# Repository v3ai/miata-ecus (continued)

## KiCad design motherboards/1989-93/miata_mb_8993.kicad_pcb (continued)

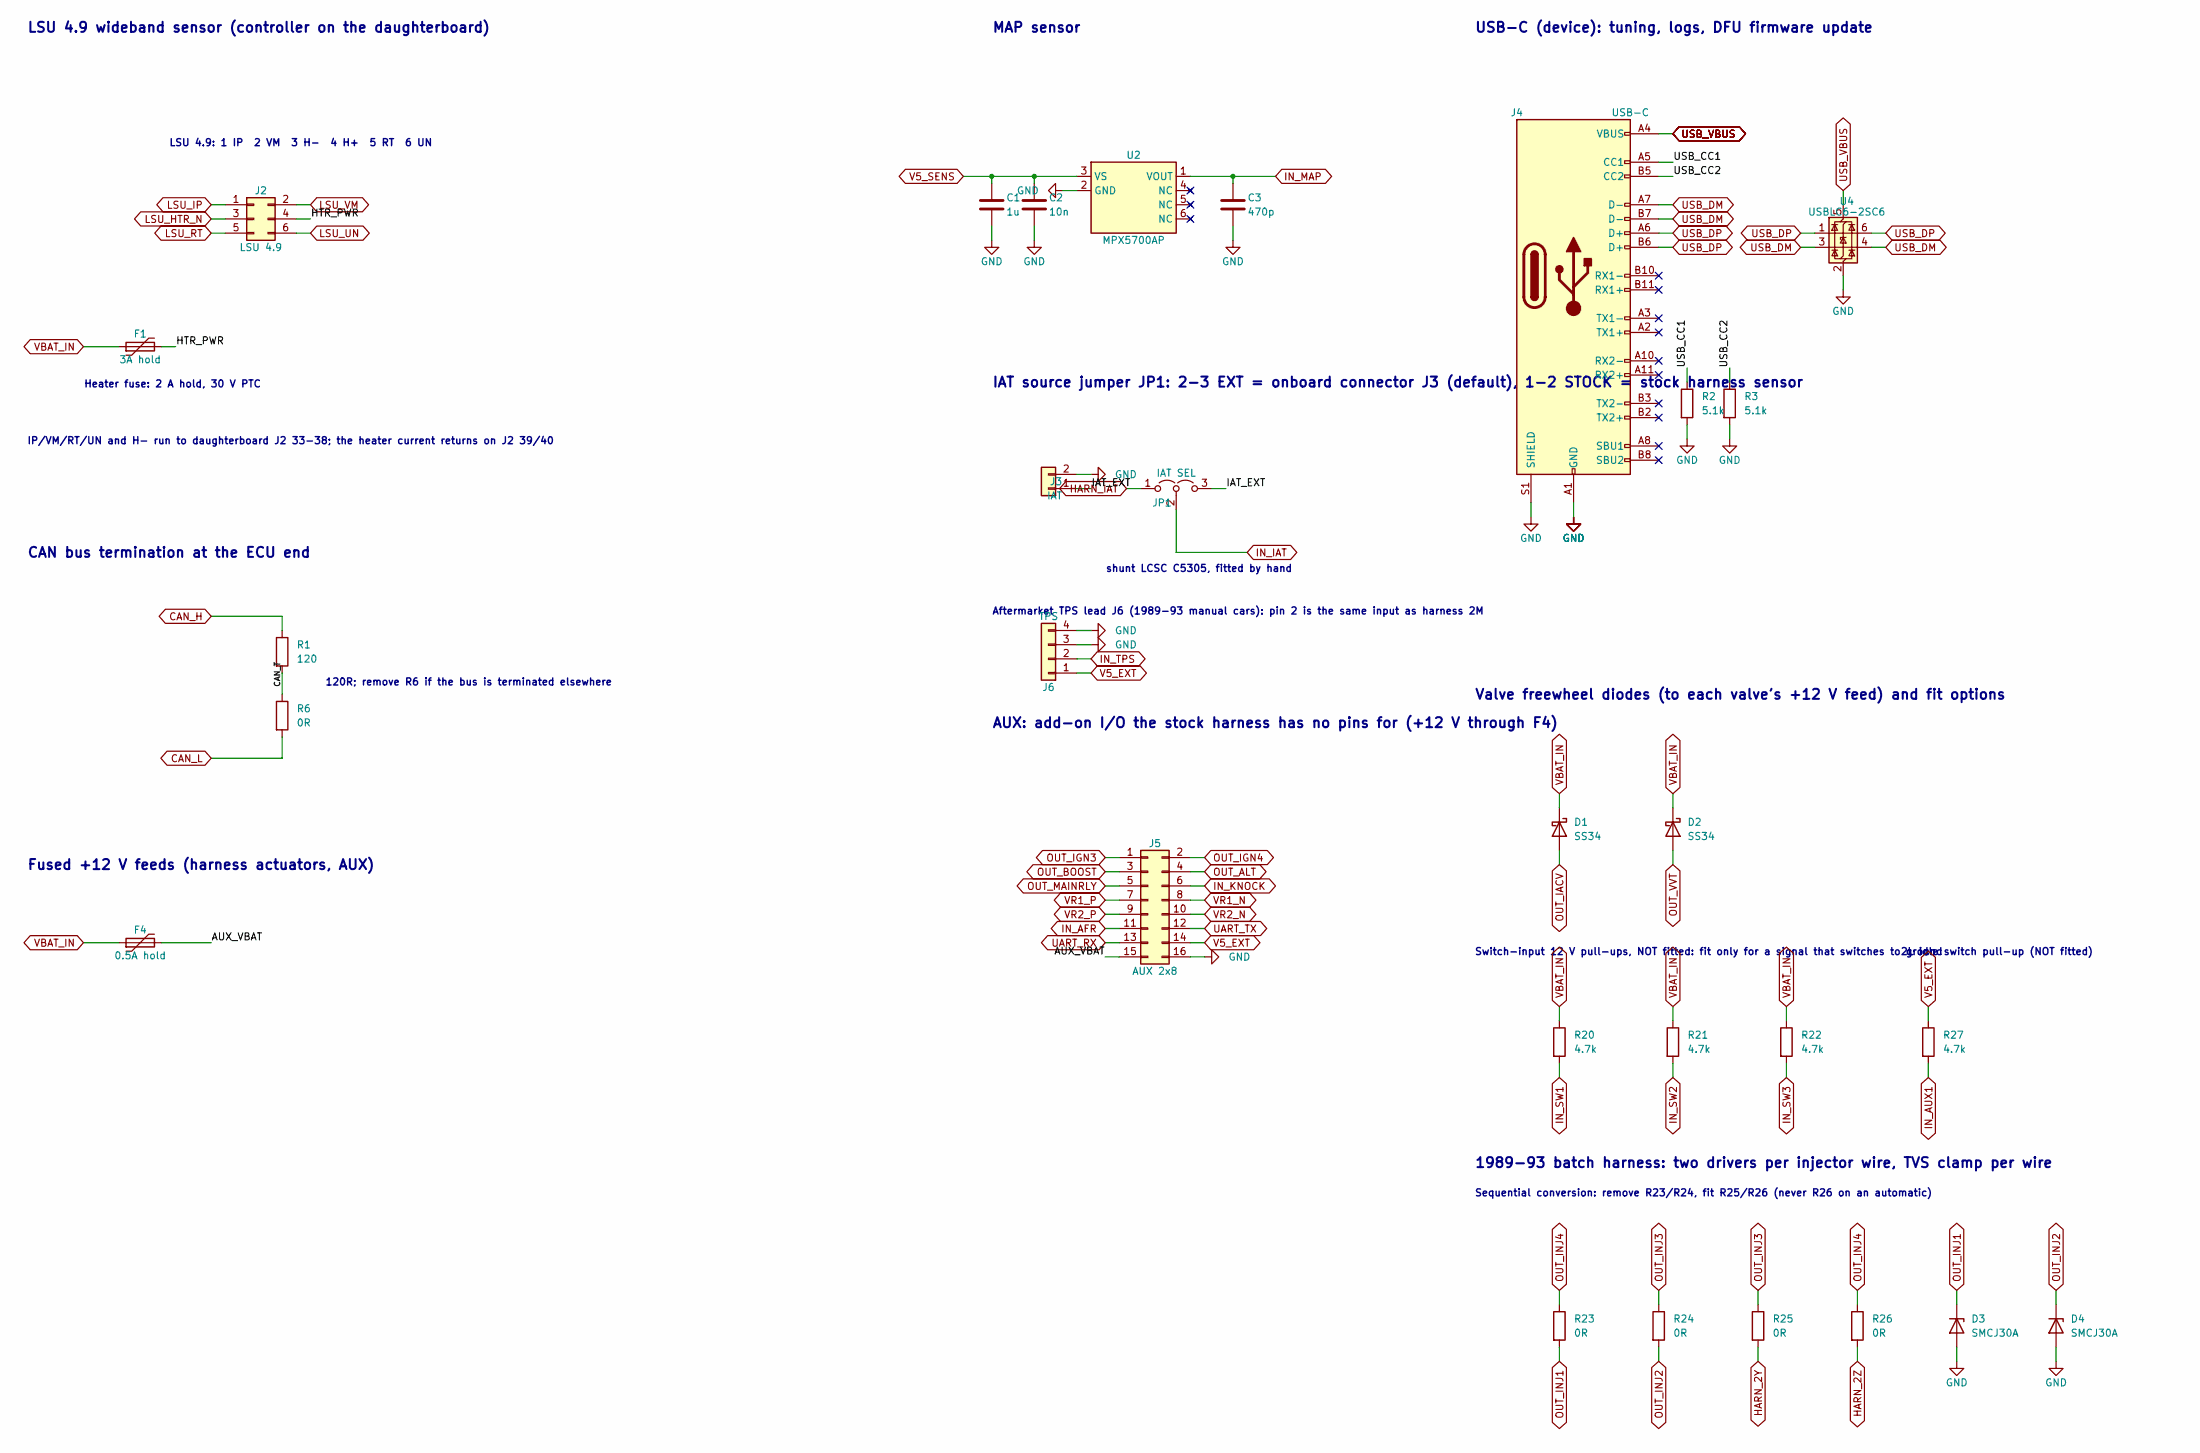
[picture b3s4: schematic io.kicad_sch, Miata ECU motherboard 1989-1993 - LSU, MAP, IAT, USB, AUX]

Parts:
C1: 1u; C_0603_1608Metric; LCSC C15849
C2: 10n; C_0603_1608Metric; LCSC C57112
C3: 470p; C_0603_1608Metric; LCSC C1620
D1, D2: SS34; D_SMA; LCSC C8678
D3, D4: SMCJ30A; D_SMC; LCSC C224048
F1: 3A hold; Fuse_2920_7451Metric; LCSC C22446884
F4: 0.5A hold; Fuse_1206_3216Metric; LCSC C70077
J2: LSU 4.9; Molex_Micro-Fit_3.0_43045-0600_2x03_P3.00mm_Horizontal; LCSC C127367
J3: IAT; Molex_Micro-Fit_3.0_43650-0200_1x02_P3.00mm_Horizontal; LCSC C587650
J4: USB-C; USB_C_GCT_USB4105_16P; LCSC C3020560
J5: AUX 2x8; IDC-Header_2x08_P2.54mm_Vertical; LCSC C3406
J6: TPS; Molex_Micro-Fit_3.0_43650-0400_1x04_P3.00mm_Horizontal; LCSC C277684
JP1: IAT SEL; PinHeader_1x03_P2.54mm_Vertical; LCSC C49257
R1: 120; R_0603_1608Metric; LCSC C22787
R2, R3: 5.1k; R_0603_1608Metric; LCSC C23186
R6: 0R; R_0603_1608Metric; LCSC C21189
R20, R21, R22, R27: 4.7k; R_0603_1608Metric
R23, R24: 0R; R_0805_2012Metric; LCSC C17477
R25, R26: 0R; R_0805_2012Metric
U2: MPX5700AP; MPX5700AP_867B_Flat; LCSC C90152
U4: USBLC6-2SC6; SOT-23-6; LCSC C7519

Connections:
/LSU, MAP, IAT, USB, AUX/AUX_VBAT: F4.2, J5.15
/LSU, MAP, IAT, USB, AUX/CAN_T: R1.2, R6.1
/LSU, MAP, IAT, USB, AUX/HTR_PWR: F1.2, J2.4
/LSU, MAP, IAT, USB, AUX/IAT_EXT: J3.1, JP1.3 (B)
/LSU, MAP, IAT, USB, AUX/USB_CC1: J4.A5 (CC1), R2.1
/LSU, MAP, IAT, USB, AUX/USB_CC2: J4.B5 (CC2), R3.1
CAN_H: R1.1; also elsewhere on the board
CAN_L: R6.2; also elsewhere on the board
GND: C1.2, C2.2, C3.2, D3.2 (A), D4.2 (A), J3.2, J4.A1 (GND), J4.A12 (GND), J4.B1 (GND), J4.B12 (GND), J4.S1 (SHIELD), J5.16, J6.3, J6.4, R2.2, R3.2, U2.2 (GND), U4.2 (GND); also elsewhere on the board
HARN_2Y: R25.2; also elsewhere on the board
HARN_2Z: R26.2; also elsewhere on the board
HARN_IAT: JP1.1 (A); also elsewhere on the board
IN_AFR: J5.11; also elsewhere on the board
IN_AUX1: R27.2; also elsewhere on the board
IN_IAT: JP1.2 (C); also elsewhere on the board
IN_KNOCK: J5.6; also elsewhere on the board
IN_MAP: C3.1, U2.1 (VOUT); also elsewhere on the board
IN_SW1: R20.2; also elsewhere on the board
IN_SW2: R21.2; also elsewhere on the board
IN_SW3: R22.2; also elsewhere on the board
IN_TPS: J6.2; also elsewhere on the board
LSU_HTR_N: J2.3; also elsewhere on the board
LSU_IP: J2.1; also elsewhere on the board
LSU_RT: J2.5; also elsewhere on the board
LSU_UN: J2.6; also elsewhere on the board
LSU_VM: J2.2; also elsewhere on the board
OUT_ALT: J5.4; also elsewhere on the board
OUT_BOOST: J5.3; also elsewhere on the board
OUT_IACV: D1.2 (A); also elsewhere on the board
OUT_IGN3: J5.1; also elsewhere on the board
OUT_IGN4: J5.2; also elsewhere on the board
OUT_INJ1: D3.1 (K), R23.2; also elsewhere on the board
OUT_INJ2: D4.1 (K), R24.2; also elsewhere on the board
OUT_INJ3: R24.1, R25.1; also elsewhere on the board
OUT_INJ4: R23.1, R26.1; also elsewhere on the board
OUT_MAINRLY: J5.5; also elsewhere on the board
OUT_VVT: D2.2 (A); also elsewhere on the board
UART_RX: J5.13; also elsewhere on the board
UART_TX: J5.12; also elsewhere on the board
USB_DM: J4.A7 (D-), J4.B7 (D-), U4.3 (I/O2), U4.4 (I/O2); also elsewhere on the board
USB_DP: J4.A6 (D+), J4.B6 (D+), U4.1 (I/O1), U4.6 (I/O1); also elsewhere on the board
USB_VBUS: J4.A4 (VBUS), J4.A9 (VBUS), J4.B4 (VBUS), J4.B9 (VBUS), U4.5 (VBUS); also elsewhere on the board
V5_EXT: J5.14, J6.1, R27.1; also elsewhere on the board
V5_SENS: C1.1, C2.1, U2.3 (VS); also elsewhere on the board
VBAT_IN: D1.1 (K), D2.1 (K), F1.1, F4.1, R20.1, R21.1, R22.1; also elsewhere on the board
VR1_N: J5.8; also elsewhere on the board
VR1_P: J5.7; also elsewhere on the board
VR2_N: J5.10; also elsewhere on the board
VR2_P: J5.9; also elsewhere on the board

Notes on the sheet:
LSU 4.9 wideband sensor (controller on the daughterboard)
LSU 4.9: 1 IP 2 VM 3 H- 4 H+ 5 RT 6 UN
IP/VM/RT/UN and H- run to daughterboard J2 33-38; the heater current returns on J2 39/40
Heater fuse: 2 A hold, 30 V PTC
CAN bus termination at the ECU end
120R; remove R6 if the bus is terminated elsewhere
MAP sensor
IAT source jumper JP1: 2-3 EXT = onboard connector J3 (default), 1-2 STOCK = stock harness sensor
shunt LCSC C5305, fitted by hand
Aftermarket TPS lead J6 (1989-93 manual cars): pin 2 is the same input as harness 2M
USB-C (device): tuning, logs, DFU firmware update
Fused +12 V feeds (harness actuators, AUX)
AUX: add-on I/O the stock harness has no pins for (+12 V through F4)
Valve freewheel diodes (to each valve's +12 V feed) and fit options
Switch-input 12 V pull-ups, NOT fitted: fit only for a signal that switches to ground
2L idle switch pull-up (NOT fitted)
1989-93 batch harness: two drivers per injector wire, TVS clamp per wire
Sequential conversion: remove R23/R24, fit R25/R26 (never R26 on an automatic)

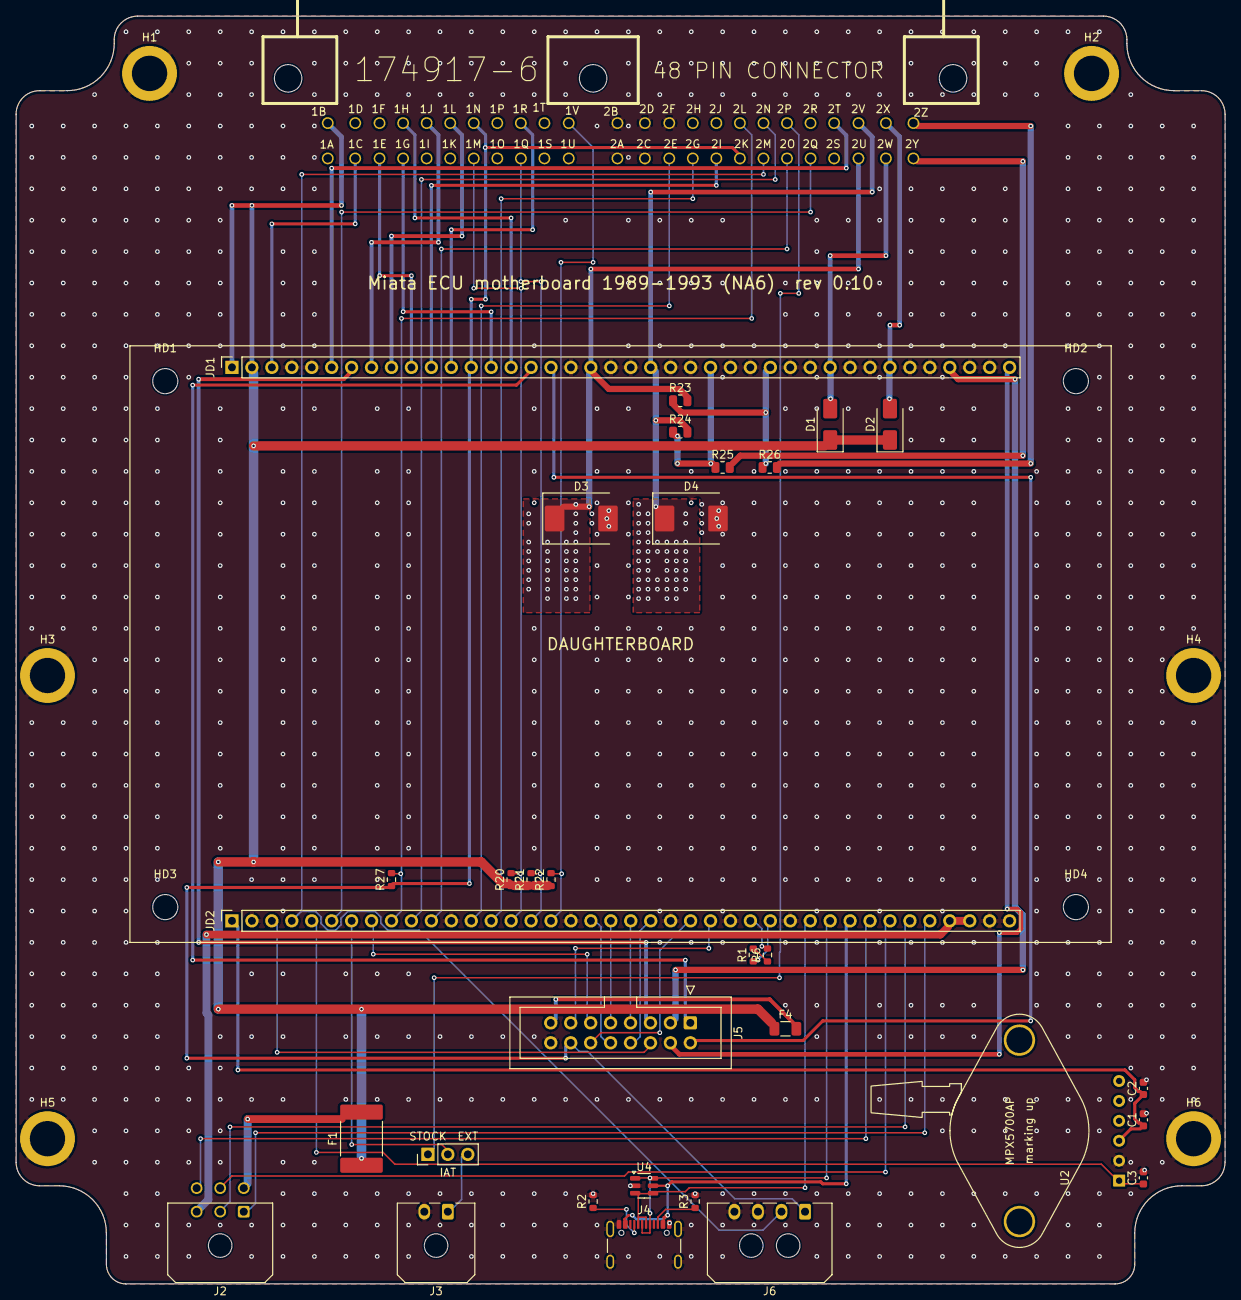
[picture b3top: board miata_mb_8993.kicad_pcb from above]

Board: 2 copper layers, 154.0 x 161.5 mm, 42 parts (0 on the bottom side), 63 nets.

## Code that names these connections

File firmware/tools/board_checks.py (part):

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Datasheet limits used (STM32F405 / F407 DS8626, STM32F103x8 DS5319; F4 family IINJ table re-confirmed in the STM32F412
datasheet, same structure):
  FT pins: VIN abs max VDD + 4.0 V; injected current -5 / +0 mA (no positive injection possible: there is no clamp
  to VDD, so the limit above VDD is the voltage, not a current). TTa (PA4/PA5) and F103 non-FT pins: VIN abs max
  4.0 V, injected current +-5 mA (diodes to VDDA / VDD). Total injected current +-25 mA. Operating range on FT pins
  -0.3..5.5 V. An FT pin used as an ADC input is treated as good to VDDA only (outside it the reading clips; tolerance
  above VDDA in analog mode is not relied on: CHECK).
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F407_NAME = {int(n): name for n, name in
             (s.split(':') for s in open(os.path.join(SCRIPTS, 'stm32f407v_lqfp100_pins.txt')).read().split())}
F407_PIN = {v: k for k, v in F407_NAME.items()}
# DS8626 pin definitions, LQFP100: every GPIO is FT except PA4/PA5 (TTa, DAC outputs); PC13-15 are FT but sit in the
# backup domain (2 MHz, 3 mA total sink/source through the power switch).
F407_TTA = {'PA4', 'PA5'}
F103_NAME = {1: 'VBAT', 2: 'PC13', 3: 'PC14', 4: 'PC15', 5: 'PD0', 6: 'PD1', 7: 'NRST', 8: 'VSSA', 9: 'VDDA',
             10: 'PA0', 11: 'PA1', 12: 'PA2', 13: 'PA3', 14: 'PA4', 15: 'PA5', 16: 'PA6', 17: 'PA7', 18: 'PB0',
             19: 'PB1', 20: 'PB2', 21: 'PB10', 22: 'PB11', 23: 'VSS', 24: 'VDD', 25: 'PB12', 26: 'PB13', 27: 'PB14',
             28: 'PB15', 29: 'PA8', 30: 'PA9', 31: 'PA10', 32: 'PA11', 33: 'PA12', 34: 'PA13', 35: 'VSS', 36: 'VDD',
             37: 'PA14', 38: 'PA15', 39: 'PB3', 40: 'PB4', 41: 'PB5', 42: 'PB6', 43: 'PB7', 44: 'BOOT0', 45: 'PB8',
             46: 'PB9', 47: 'VSS', 48: 'VDD'}
# DS5319 pin definitions: FT = PA8-PA15, PB2-PB4, PB6-PB15, PD0/PD1; not FT: PA0-PA7, PB0, PB1, PB5, PC13-PC15
F103_FT = {'PA8', 'PA9', 'PA10', 'PA11', 'PA12', 'PA13', 'PA14', 'PA15', 'PB2', 'PB3', 'PB4', 'PB6', 'PB7', 'PB8',
           'PB9', 'PB10', 'PB11', 'PB12', 'PB13', 'PB14', 'PB15', 'PD0', 'PD1'}
VDD = 3.3
LIM_FT_V = VDD + 4.0          # abs max on FT pins
LIM_NONFT_V = 4.0             # abs max on TTa / non-FT pins
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FT_OPER_MAX = 5.5
VIL, VIH = 0.3 * VDD, 0.7 * VDD   # DS8626 CMOS levels (conservative; FT inputs switch at 1.79 V by design)

ADC = {**{f'EFI_ADC_{i}': f'PA{i}' for i in range(8)}, 'EFI_ADC_8': 'PB0', 'EFI_ADC_9': 'PB1',
       **{f'EFI_ADC_{10 + i}': f'PC{i}' for i in range(6)}}

# alternate functions whose direction matters (DS8626 / DS5319 alternate-function tables)
AF_DIR = {('U1', 'PB12'): ('CAN2_RX', 'in'), ('U1', 'PB13'): ('CAN2_TX', 'out'),
          ('U1', 'PC6'): ('USART6_TX', 'out'), ('U1', 'PC7'): ('USART6_RX', 'in'),
          ('U1', 'PD8'): ('USART3_TX', 'out'), ('U1', 'PD9'): ('USART3_RX', 'in'),
          ('U102', 'PA9'): ('USART1_TX', 'out'), ('U102', 'PA10'): ('USART1_RX', 'in'),
          ('U102', 'PA11'): ('CAN_RX', 'in'), ('U102', 'PA12'): ('CAN_TX', 'out')}


def mcu_pin_info(ref, pad):
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    'vehicleSpeedSensorInputPin': 'vss', 'acSwitch': 'acSwitch', 'clutchDownPin': 'clutch',
    'tps1_1AdcChannel': 'tps', 'mafAdcChannel': 'maf', 'afr.hwChannel': 'afr', 'ignKeyAdcChannel': 'ignKey',
    'vbattAdcChannel': 'vbatt', 'clt.adcChannel': 'clt', 'iat.adcChannel': 'iat', 'map.sensor.hwChannel': 'map',
    'canTxPin': 'can2Tx', 'canRxPin': 'can2Rx',   # PB13/PB12 = CAN2 peripheral, rusEFI's first bus
}
FW_OUTPUTS = {'ign1&4', 'ign3(COP)', 'ign2&3', 'ign4(COP)', 'inj1', 'inj2', 'inj3', 'inj4', 'idle', 'fuelPump',
              'acRelay', 'fan', 'fan2', 'cel', 'tach', 'boost', 'mainRelay', 'alternator', 'vvt', 'o2heater'}
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    wb = open(os.path.join(BOARD, 'wideband_uart_flash.cpp')).read()
    for label, port in re.findall(r'efiSetPadMode\("WBO ([\w ]+)", Gpio::(\w+)', wb):
        board['wbo ' + label] = 'P' + port
    board['usbDM'], board['usbDP'], board['swdio'], board['swclk'] = 'PA11', 'PA12', 'PA13', 'PA14'
    board['uart6Tx'], board['uart6Rx'] = 'PC6', 'PC7'   # rusEFI's TS secondary / AUX UART (J5-12/13)
    return out, board, sorted(external)


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                      'o2heater', 'vvt', 'boost', 'vss', 'acSwitch', 'clutch'):
                fw[k] = kv.get(k, '-')
            fw = {k: ('P' + v if not v.startswith('P') else v) for k, v in fw.items() if v not in ('-', '')}
            if kv.get('ignKey', '-') not in ('-', ''):      # the dump names the ADC channel ("VIGN"), which is PA2
                fw['ignKey'] = 'PA2'
            out[parts[1]] = fw
    return out

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        row('FAIL', 'mating', year, f'{mb_path}: ' + '; '.join(bad[:6]))
    else:
        row('OK', 'mating', year, f'{mb_path}: all {len(dj)} J1/J2 pads land on JD1/JD2 by pure translation '
            f'({ox:.2f}, {oy:.2f} mm), same pin and net (HTR_GND -> motherboard GND by design)')


# ------------------------------------------------------------------------------------------------------------------
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    has_key = 'ignKey' in fw
    want = exp_tab.get('ignKey')
    ok = (has_key and want in vign_cav) or (not has_key and not want)
    row('OK' if ok else 'FAIL', 'reverse', year, f'ignition sense {"PA2 (AN_VIGN)" if has_key else "not configured"}; '
        f'VIGN_IN cavities wired {vign_cav or "-"}; reference {want or "none"}')
    # unused F405 GPIO with a harness path but no firmware function (informational)
    for pad, net in sorted(sysm.by_ref['U1']['pads'].items(), key=lambda kv: int(kv[0])):
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    """two drivers on one net (push-pull + anything, open drain + car output); intentional open-drain pairs."""
    res = research.get(RESEARCH_YEAR.get(year, ''), {})
    out_ports = {p for f, p in fw.items() if f in FW_OUTPUTS} | {board_fw[k] for k in board_fw if k.startswith('led')} \
        | {board_fw['wbo BOOT0'], 'PB13', 'PC6', 'PD8'}
    od_ports = {board_fw['drvEnable'], board_fw['wbo NRST']}
    drv = collections.defaultdict(list)    # net -> [(who, kind)]  kind: pp / od
    for p in sysm.parts:
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                    drv[net].append((f'U1 {name}', 'pp'))
            elif ref == 'U102':
                name = mcu_pin_info('U102', pad)[0]
                if name in ('PA6', 'PB10', 'PB5', 'PB6', 'PB7', 'PB8', 'PB9', 'PA9', 'PA12'):
                    drv[net].append((f'U102 {name}', 'pp'))
            elif val == 'ULN2003AD' and pad in ('10', '11', '12', '13', '14', '15', '16'):
                drv[net].append((f'{ref}.{pad}', 'od'))
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                   '5': ('+5V', 'ADJ reference')},
    'LMR14020': {'3': ('+12V_F', 'EN (tie to VIN or divider)'), '7': ('GND', 'GND'), '9': ('GND', 'exposed pad')},
    'SN74LVC4245APWR': {'2': ('GND', 'DIR: low = B->A'), '22': ('DRV_EN_N', 'OE')},
    'STM32F405VGT6': {'94': ('BOOT0', 'BOOT0 pulled down'), '37': ('BOOT1', 'PB2/BOOT1 pulled down'),
                      '20': ('GND', 'VSSA'), '21': ('+3V3A', 'VREF+'), '22': ('+3V3A', 'VDDA'),
                      '49': ('VCAP1', 'VCAP1'), '73': ('VCAP2', 'VCAP2'), '6': ('+3V3', 'VBAT')},
    'STM32F103C8T6': {'1': ('+3V3', 'VBAT'), '8': ('GND', 'VSSA'), '9': ('WB_VDDA', 'VDDA'), '44': ('WB_BOOT0', 'BOOT0'),
                      '20': ('WB_BOOT1', 'PB2/BOOT1')},
    'SN65HVD230DR': {'8': ('GND', 'Rs: GND = high speed (open would be standby? low-power mode)')},
    'TJA1042T/3/1J': {'3': ('+5V', 'VCC 4.5-5.5 V'), '5': ('+3V3', 'VIO = MCU I/O level'),
                      '8': ('GND', 'STB: low = normal mode (internal pull-up would select standby)'), '2': ('GND', 'GND')},
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    ('LM2903DR', ['2', '3', '5', '6'], 'LM2903 input', True, 'unused VR channel must sit at a defined level'),
    ('LMV321IDBVR', ['1', '3'], 'LMV321 input', True, 'knock amp bias'),
    ('STM32F405VGT6', ['94', '37'], 'F405 BOOT0/BOOT1', True, 'boot mode'),
    ('STM32F103C8T6', ['44', '20'], 'F103 BOOT0/BOOT1', True, 'boot mode (BOOT0 is driven by the F405 PD10, high-Z in reset)'),
]


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        relay = [c for c, n in sysm.cavity.items() if n == 'OUT_MAINRLY' and c not in year_unwired(year)]
        txt = f'ignition wake: {vi} -> D8 -> F1: +12V {V["+12V"]:.2f} V with the main relay open'
        if hold:
            txt += f'; firmware holds the main relay on {relay} ({hold}) and reads the key on PA2'
        row('OK' if V['+12V'] > 12 else 'FAIL', 'power', year, txt)
    elif fw.get('mainRelay'):
        row('FAIL', 'power', year, 'firmware drives a main relay but no ignition wake cavity is wired')
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    dc.fix('_HALF', 1.65)
    dc.fix('_MAP', 0.85)
    out_ports = {p for f, p in fw.items() if f in FW_OUTPUTS} | {board_fw[k] for k in board_fw if k.startswith('led')} \
        | {board_fw['wbo BOOT0'], 'PB13', 'PC6', 'PD8'}
    for p in sysm.parts:
        ref, val, pads, fp = p['ref'], p['value'], p['pads'], p['fp']
        base = ref.split('.')[-1]
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                    dc.d(net, vdd, 0.5, 10, tag=('MCU+', ref, k))
                if ref == 'U1' and name in out_ports:
                    dc.r(net, '+3V3' if states.get(f'U1.{name}') == 'high' else 'GND', 40, tag=('MCU_OUT', ref, k))
                if ref == 'U102' and name == 'PB10':
                    dc.r(net, 'GND', 40)
                if ref == 'U102' and name == 'PA6':
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
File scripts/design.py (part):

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J1 = {1: 'VBAT_IN', 2: 'VBAT_IN', 3: 'VIGN_IN', 4: 'GND', 5: 'GND',
      6: 'OUT_FP', 7: 'OUT_MAINRLY', 8: 'OUT_AC', 9: 'OUT_FAN', 10: 'OUT_CEL',
      11: 'OUT_TACH', 12: 'OUT_LS7',
      # rev 0.8: pin 13 (was GND) carries the harness sensor 5 V (V5_EXT, its own protected tracker U14), so a
      # harness 5 V wire shorted to battery no longer back-feeds the on-board MAP sensor (V5_SENS, J2-1)
      13: 'V5_EXT',
      14: 'OUT_IGN1', 15: 'OUT_IGN2', 16: 'OUT_IGN3', 17: 'OUT_IGN4', 18: 'GND'}
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    '21': '+3V3A', '22': '+3V3A',
    '49': 'VCAP1', '73': 'VCAP2',
    '12': 'HSE_IN', '13': 'HSE_OUT', '14': 'NRST', '94': 'BOOT0',
    # relay/lamp outputs from the top of the left edge (ULN2003 sits up-left). PC13/PC14 run through the backup
    # power switch, which can supply 3 mA in total; the two ULN2003 inputs draw at most ~0.72 mA each at 3.3 V
    # ((3.3 - 2 Vbe) / 2.7k), so 1.45 mA together, and relays need no speed (ST's limit there is 2 MHz).
    '1': 'LS7_CTL', '2': 'TACH_CTL', '3': 'CEL_CTL', '4': 'FAN_CTL', '5': 'AC_CTL',
    '7': 'MAINRLY_CTL', '8': 'FP_CTL',
    # rev 0.5: PB2 is BOOT1; pulled low so ST's DFU bootloader starts reliably (BOOT0 = 1, BOOT1 = 0)
    '37': 'BOOT1',
    # rev 0.5: low-side driver enable (PA8, active low, pulled up to +5V: drivers off until firmware enables).
    # On the right edge, so it reaches U11's ~OE from below instead of adding a ninth line to the top-edge bundle.
    '67': 'DRV_EN_N',
    # ignition + smart low sides from the top edge, ordered left->right like the driver row
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    '93': 'INJ1_CTL', '92': 'INJ2_CTL', '91': 'INJ3_CTL', '90': 'INJ4_CTL',
    '89': 'IACV_CTL', '88': 'VVT_CTL', '87': 'BOOST_CTL', '86': 'ALT_CTL',
    # analog: all nine sensor inputs on the bottom edge in J2 column order, knock on
    # PA3 (ADC3_IN3); battery/ignition sense on the left edge next to their divider
    '26': 'AN_KNOCK', '29': 'AN_TPS', '30': 'AN_MAP', '31': 'AN_CLT', '32': 'AN_IAT',
    '33': 'AN_AFR', '34': 'AN_AUX1', '35': 'AN_AUX2', '36': 'AN_AUX3',
    '24': 'AN_VBATT', '25': 'AN_VIGN',
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    '38': 'HALL1', '39': 'HALL2', '40': 'SW1', '41': 'SW2', '42': 'SW3',
    '43': 'VR2_OUT', '44': 'VR1_OUT',
    # comms (right edge)
    '51': 'CAN_RX', '52': 'CAN_TX',            # CAN2 PB12/PB13
    # rev 0.10: PC6 / PC7 are the flex-fuel sensor and nitrous arming inputs (they were a spare UART); same 10k + clamps
    '63': 'FLEX_M', '64': 'N2O_ARM_M',
    # rev 0.10: microSD on SPI2 (PB10 SCK, PB14 MISO, PB15 MOSI; CS on PD13)
    '47': 'SD_SCK', '53': 'SD_MISO', '54': 'SD_MOSI', '60': 'SD_CS',
    # LEDs: run PD12, error PD15; rev 0.8 moved comms and warning to PC8/PC9 (PD13/PD14 left no route to the LED column)
    '59': 'LED_RUN', '65': 'LED_COMM', '66': 'LED_WARN', '62': 'LED_ERR',
    # wideband MCU programming link (rev 0.4): USART3 on PD8/PD9 to the wideband MCU's ROM-bootloader USART1 (F103 since rev 0.6)
    # (PA10/PA9), PD10 drives its BOOT0 (10k pull-down stays), PD11 (open drain) its NRST
    '55': 'WB_PROG_TX', '56': 'WB_PROG_RX', '57': 'WB_BOOT0', '58': 'WB_NRST',
    '70': 'USB_DM', '71': 'USB_DP',            # OTG_FS PA11/PA12
    '72': 'SWDIO', '76': 'SWCLK',              # PA13/PA14
}
add('U1', 'STM32F405VGT6', 'LQFP100', 'C56621', mcu, 'MCU, 168MHz Cortex-M4F, 1MB flash')

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    R(f'R{rn}', '10k', 'AN_' + n, 'GND', '0402'); rn += 1
    C(f'C{cn}', '10n', 'AN_' + n, 'GND', '0402'); cn += 1
    if n in ('CLT', 'IAT'):     # rev 0.8: bias from the harness sensor supply V5_EXT (the sensors are harness parts)
        R(f'R{rn}', '2.7k', 'V5_EXT', 'IN_' + n, '0603'); rn += 1

# knock: AC coupled, biased to 1.65V, gain 5.7. Rev 0.7: the coupling cap follows R138 (2.2k, see the rev 0.7 block)
C(f'C{cn}', '100n', 'KN_IN', 'KN_P'); cn += 1
R(f'R{rn}', '100k', 'KN_P', 'KN_BIAS'); rn += 1
R(f'R{rn}', '100k', '+3V3', 'KN_BIAS'); rn += 1
R(f'R{rn}', '100k', 'KN_BIAS', 'GND'); rn += 1
C(f'C{cn}', '1u', 'KN_BIAS', 'GND'); cn += 1
R(f'R{rn}', '47k', 'KN_OUT', 'KN_N'); rn += 1
R(f'R{rn}', '10k', 'KN_N', 'KN_BIAS'); rn += 1
R(f'R{rn}', '330', 'KN_OUT', 'AN_KNOCK'); rn += 1
C(f'C{cn}', '10n', 'AN_KNOCK', 'GND'); cn += 1
C(f'C{cn}', '100n', '+3V3', 'GND'); cn += 1
add('U8', 'LMV321IDBVR', 'SOT235', 'C7972',
    {'1': 'KN_P', '2': 'GND', '3': 'KN_N', '4': 'KN_OUT', '5': '+3V3'}, 'knock amp')
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# 2 x 5.1k to the comparator inputs, 1 nF across them, a BAT54S on each input to GND and +5V (holds them at -0.3..5.3 V;
# the LM2903 inputs take up to 36 V and down to -0.3 V), 100k from each input to VBIAS (1.65 V), and 1M from the
# open-collector output back to IN+ for about 30 mV of hysteresis. Output high when harness - is above harness +
# (the MAX9926's polarity), 10k pull-up to +3V3 into PE13/PE12. See firmware/tools/circuit_sim.py section H.
# comparator A (pins 1-3) takes VR2 and B (5-7) VR1, so each channel's pins face its own header columns
add('U9', 'LM2903DR', 'SOIC8', 'C7549',
    {'1': 'VR2_OUT', '2': 'VR2_INN', '3': 'VR2_INP', '4': 'GND',
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    R(f'R{rn}', '4.7k', 'IN_' + n, n, '0603'); rn += 1
    R(f'R{rn}', '1k', f'V5_H{k + 1}', 'IN_' + n, '0603'); rn += 1
    C(f'C{cn}', '1n', n, 'GND', '0402'); cn += 1
# rev 0.5: clamp diodes to +3V3 (PE7/PE8 are 5 V-tolerant pins with no clamp of their own; a crank/cam wire
# shorted to battery would otherwise put ~14 V on them). 4.7k limits the clamp current to ~2 mA.
add('D13', '1N4148WS', 'SOD323', 'C2128', {'1': '+3V3', '2': 'HALL1'}, 'HALL1 clamp to +3V3')
add('D14', '1N4148WS', 'SOD323', 'C2128', {'1': '+3V3', '2': 'HALL2'}, 'HALL2 clamp to +3V3')
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C('C57', '100n', '+5V', 'GND', '0402')        # U11 VCCA
C('C58', '100n', '+3V3', 'GND', '0402')       # U11 VCCB
R('R71', '10k', '+5V', 'DRV_EN_N', '0402')    # drivers disabled until the firmware pulls DRV_EN_N low
R('R72', '10k', 'BOOT1', 'GND', '0402')       # PB2 / BOOT1 low
# The MCU-side control lines have no pull-downs (no room between the MCU and U11). While U11 is disabled its
# outputs are high-impedance and R19-R26 hold the drivers off, so a floating MCU pin does nothing. Once enabled,
# the board firmware parks every control pin rusEFI isn't using as an input with pull-down (rusEFI's own
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# AUX header UART (J2 24/25 -> motherboard J5): 10k in series and a BAT54S clamp at the MCU side, so the header pins
# survive car wiring shorted to battery (about 55 mW in the resistor at 24 V; 4.7k took 120 mW, over the 0603's 100 mW);
# 10k + ~50 pF of header and cable is 0.5 us, fine at 115200 baud (8.7 us per bit)
# Rev 0.10: the two pins are general 0-12 V digital inputs now: flex-fuel sensor (PC6, EXTI line 6 is free; PC7 would
# share line 7 with the crank input on PE7) and the nitrous arming switch (PC7, polled). Pull-ups are on the motherboard.
R('R139', '10k', 'FLEX_M', 'IN_FLEX')
R('R140', '10k', 'N2O_ARM_M', 'IN_N2O')
add('D36', 'BAT54S', 'SOT23', 'C19726', {'1': 'GND', '2': '+3V3', '3': 'FLEX_M'}, 'flex input clamp')
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R('R161', '47k', '+3V3', 'SD_MOSI', '0402')
R('R162', '47k', '+3V3', 'SD_DAT1', '0402')
R('R163', '47k', '+3V3', 'SD_DAT2', '0402')
# battery / ignition sense clamps: in a 24 V jump start the divider put 4.0 V on PA1 (analog mode, VDDA + 0.3 V max)
add('D38', 'BAT54WS', 'SOD323', 'C124205', {'1': '+3V3', '2': 'AN_VBATT'}, 'AN_VBATT clamp to +3V3')
add('D39', 'BAT54WS', 'SOD323', 'C124205', {'1': '+3V3', '2': 'AN_VIGN'}, 'AN_VIGN clamp to +3V3')
# +3V3 shunt clamp: every clamp on the board (analog, hall, switch, UART, the wideband's pump/Vm drive) dumps a fault
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
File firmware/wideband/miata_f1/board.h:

/*
    ChibiOS - Copyright (C) 2006..2018 Giovanni Di Sirio

    Licensed under the Apache License, Version 2.0 (the "License");
    you may not use this file except in compliance with the License.
    You may obtain a copy of the License at

        http://www.apache.org/licenses/LICENSE-2.0

    Unless required by applicable law or agreed to in writing, software
    distributed under the License is distributed on an "AS IS" BASIS,
    WITHOUT WARRANTIES OR CONDITIONS OF ANY KIND, either express or implied.
    See the License for the specific language governing permissions and
    limitations under the License.
*/

#ifndef _BOARD_H_
#define _BOARD_H_

/*
 * Board identifier.
 */
#define BOARD_NAME                  "miata-ecus daughterboard wideband (STM32F103C8)"

/*
 * Board oscillators-related settings.
 * NOTE: LSE not fitted.
 * HSE: 8 MHz crystal Y101.
 */
#if !defined(STM32_LSECLK)
#define STM32_LSECLK                0U
#endif

#if !defined(STM32_HSECLK)
#define STM32_HSECLK                8000000U
#endif

/*
 * MCU type: STM32F103C8T6 / CBT6 (medium density, 64/128 KB flash, 20 KB RAM, LQFP48).
 */
#define STM32F103xB

/*
 * I/O ports initial setup, this configuration is established soon after reset
 * in the initialization code.
 *
 * The digits have the following meaning:
 *   0 - Analog input.
 *   1 - Push Pull output 10MHz.
 *   2 - Push Pull output 2MHz.
 *   3 - Push Pull output 50MHz.
 *   4 - Digital input.
 *   5 - Open Drain output 10MHz.
 *   6 - Open Drain output 2MHz.
 *   7 - Open Drain output 50MHz.
 *   8 - Digital input with PullUp or PullDown resistor depending on ODR.
 *   9 - Alternate Push Pull output 10MHz.
 *   A - Alternate Push Pull output 2MHz.
 *   B - Alternate Push Pull output 50MHz.
 *   C - Reserved.
 *   D - Alternate Open Drain output 10MHz.
 *   E - Alternate Open Drain output 2MHz.
 *   F - Alternate Open Drain output 50MHz.
 * Please refer to the STM32 Reference Manual for details.
 */

/*
 * Port A setup (the analog front end is the rusEFI/FOME wideband module, rev C).
 * PA0  - Un_sense (Nernst, x2.7)   (analog in, ADC12_IN0).
 * PA1  - not connected (rev 0.7; the module wired it to LSU_Vm, never sampled).
 * PA2  - Ip_sense                  (analog in, ADC12_IN2).
 * PA3  - Vm_sense (virtual ground) (analog in, ADC12_IN3).
 * PA4, PA5 - unused                (input, pull-up).
 * PA6  - Ip_dac PWM, TIM3_CH1      (alternate pushpull, 50 MHz).
 * PA7, PA8 - unused                (input, pull-up).
 * PA9  - USART1_TX                 (input, pull-up: only the ROM bootloader uses it, for flashing from the ECU).
 * PA10 - USART1_RX                 (input, pull-up).
 * PA11 - CAN_RX                    (input, pull-up).
 * PA12 - CAN_TX                    (alternate pushpull, 50 MHz).
 * PA13 - SWDIO, PA14 - SWCLK, PA15 - unused (JTDI).
 */
#define VAL_GPIOACRL            0x8B880000      /*  PA7...PA0 */
#define VAL_GPIOACRH            0x888B8888      /* PA15...PA8 */
#define VAL_GPIOAODR            0x0000FFFF

/*
 * Port B setup.
 * PB0  - Vbatt_sense, 100k/10k     (analog in, ADC12_IN8).
 * PB1  - unused                    (input, pull-up).
 * PB2  - BOOT1, 10k to GND (R135)  (input, floating).
 * PB3, PB4 - unused (JTDO, NJTRST) (input, pull-up).
 * PB5  - Nernst 4.2 ESR drive, 6.8k (input, floating: high-Z until selected).
 * PB6  - Nernst ADV ESR drive, 47k (input, floating: high-Z until selected).
 * PB7  - Nernst 4.9 ESR drive, 22k (output pushpull, 50 MHz: the default sensor).
 * PB8  - LED_BLUE                  (output pushpull, 2 MHz, starts off).
 * PB9  - LED_GREEN                 (output pushpull, 2 MHz, starts off).
 * PB10 - heater PWM, TIM2_CH3      (alternate pushpull, 50 MHz; TIM2 partial remap 2, set in boardInit).
 * PB11..PB15 - unused              (input, pull-up).
 */
#define VAL_GPIOBCRL            0x34488480      /*  PB7...PB0 */
#define VAL_GPIOBCRH            0x88888B22      /* PB15...PB8 */
#define VAL_GPIOBODR            0x0000FCFF

/*
 * Port C setup.
 * PC13 - ID_SEL1, PC14 - ID_SEL2   (digital input, not connected: "floating" strap = default CAN index).
 * PC15 - unused                    (input, pull-up). PC0..PC12 are not bonded on LQFP48.
 */
#define VAL_GPIOCCRL            0x88888888      /*  PC7...PC0 */
#define VAL_GPIOCCRH            0x84488888      /* PC15...PC8 */
#define VAL_GPIOCODR            0x0000FFFF

/*
 * Port D setup.
 * PD0, PD1 - OSC_IN / OSC_OUT (crystal).
 */
#define VAL_GPIODCRL            0x88888844      /*  PD7...PD0 */
#define VAL_GPIODCRH            0x88888888      /* PD15...PD8 */
#define VAL_GPIODODR            0x0000FFFF

/*
 * Port E setup (not bonded on LQFP48).
 */
#define VAL_GPIOECRL            0x88888888      /*  PE7...PE0 */
#define VAL_GPIOECRH            0x88888888      /* PE15...PE8 */
#define VAL_GPIOEODR            0x0000FFFF

/*
 * USB bus activation macro, required by the USB driver.
 */
#define usb_lld_connect_bus(usbp)

/*
 * USB bus de-activation macro, required by the USB driver.
 */
#define usb_lld_disconnect_bus(usbp)

#if !defined(_FROM_ASM_)
#ifdef __cplusplus
extern "C" {
#endif
  void boardInit(void);
#ifdef __cplusplus
}
#endif
#endif /* _FROM_ASM_ */

#endif /* _BOARD_H_ */

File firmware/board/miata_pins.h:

/**
 * @file miata_pins.h
 * @brief Pin map of the miata-ecus daughterboard (rev 0.10; rev 0.9 boards run the same firmware: the pins added in
 * rev 0.10 are not connected there). Must match scripts/design.py ("mcu" dict);
 * firmware/tools/check_pins.py cross-checks the two.
 */

#pragma once

// ---------------------------------------------------------------------------------------------------------------
// Pin map (daughterboard rev 0.8; the MCU pins are unchanged since rev 0.5)
// ---------------------------------------------------------------------------------------------------------------
// Ignition: TC4427 5 V push-pull drivers, active high. The stock harness only has IGN1 (coil pack 1&4) and IGN2 (2&3).
// Rev 0.8: each output sources through 100 R + a Schottky and has a protected low-side pull-down (ZXMS6004, gate from
// an inverter), so a coil wire shorted to battery no longer back-drives the TC4427.
#define MIATA_IGN1 Gpio::E1
#define MIATA_IGN2 Gpio::E0
#define MIATA_IGN3 Gpio::B9
#define MIATA_IGN4 Gpio::B8
// Protected low sides, active high: ST VND7NV04 (rev 0.8; NCV8406A in rev 0.5b-0.7, AUIPS2041L before), driven at 5 V
// through an SN74LVC4245A whose output enable is MIATA_DRV_EN (open drain, active low, pulled up to 5 V): all eight
// stay off until the firmware enables them.
#define MIATA_INJ1 Gpio::B7
#define MIATA_INJ2 Gpio::B6
#define MIATA_INJ3 Gpio::B5
#define MIATA_INJ4 Gpio::B4
#define MIATA_IACV Gpio::B3
#define MIATA_VVT Gpio::D7    // NB2 OCV; 1996-97 and NB1 front O2 heater; 1989-93 purge
#define MIATA_BOOST Gpio::D6  // AUX header only
#define MIATA_ALT Gpio::D5    // NB alternator field; 1994-95 pressure regulator solenoid
// Relay / lamp / tach outputs, active high: ZXMS6004 protected low sides (rev 0.8; a ULN2003 before), driven at 5 V
// through a second SN74LVC4245A (U12) on the same MIATA_DRV_EN enable, so they too stay off until the firmware
// enables the drivers.
#define MIATA_FP Gpio::C14      // backup-domain pin: drives a CMOS shifter input (no load; ST's switch limit 3 mA). Also OSC32_IN: the LSE is kept off (board/mcuconf.h)
#define MIATA_MAINRLY Gpio::C13 // 2003-05 main relay; NB1 VICS solenoid
#define MIATA_AC Gpio::E6
#define MIATA_FAN Gpio::E5
#define MIATA_CEL Gpio::E4
#define MIATA_TACH Gpio::E3
#define MIATA_LS7 Gpio::E2      // second fan / condenser fan relay
// Low-side driver enable (PA8): drive low to enable the eight low-side driver inputs.
#define MIATA_DRV_EN Gpio::A8
// Digital inputs.
#define MIATA_HALL1 Gpio::E7    // crank (NA: CAS SGT, NB: CKP), 1k pull-up to the harness 5 V through a Schottky, clamped to 3.3 V
#define MIATA_HALL2 Gpio::E8    // cam (NA: CAS SGC, NB: CMP)
#define MIATA_SW1 Gpio::E9      // 12 V input through 22k/10k (rev 0.8; 33k/10k before): vehicle speed on every motherboard
#define MIATA_SW2 Gpio::E10     // A/C switch
#define MIATA_SW3 Gpio::E11     // clutch switch
// rev 0.10: two more 0-12 V inputs on J2 pins 24/25 (10k in series, clamped to 3.3 V; a spare UART up to rev 0.9).
#define MIATA_FLEX Gpio::C6     // flex-fuel sensor (50-150 Hz). The motherboard pulls the line up to the sensor 5 V (4.7k); 10 us filter
#define MIATA_N2O_ARM Gpio::C7  // nitrous arming switch to 12 V. The motherboard pulls the line down (10k); 100 us filter
// rev 0.10: microSD socket on SPI2 (microRusEFI's arrangement, with the clock on PB10 because PB13 is the CAN transmit pin).
#define MIATA_SD_SCK Gpio::B10
#define MIATA_SD_MISO Gpio::B14
#define MIATA_SD_MOSI Gpio::B15
#define MIATA_SD_CS Gpio::D13
// Analog inputs (0-5 V through 5.6k/10k, so x1.56 at the ADC).
#define MIATA_IN_VBATT EFI_ADC_1   // PA1, 33k/6.8k; rev 0.10: from the battery input itself (up to rev 0.9 after D7 and the fuse, 0.3-0.6 V low)
#define MIATA_IN_VIGN EFI_ADC_2    // PA2, 33k/6.8k
#define MIATA_IN_TPS EFI_ADC_4     // PA4
#define MIATA_IN_MAP EFI_ADC_5     // PA5, on-board MPX5700AP
#define MIATA_IN_CLT EFI_ADC_6     // PA6, 2.7k pull-up to the harness 5 V (V5_EXT, rev 0.8: a second TLS115 tracking +5V)
#define MIATA_IN_IAT EFI_ADC_7     // PA7, 2.7k pull-up: the car's own air-temperature sensor
#define MIATA_IN_AFR EFI_ADC_14    // PC4, external 0-5 V wideband (the on-board one talks CAN)
#define MIATA_IN_AUX1 EFI_ADC_15   // PC5, rear O2 / idle switch / load signal, depending on year
#define MIATA_IN_AUX2 EFI_ADC_8    // PB0, front narrowband O2
#define MIATA_IN_AUX3 EFI_ADC_9    // PB1, AFM flap or MAF signal

// Board voltages and dividers.
static constexpr float MIATA_VBATT_DIVIDER = (33.0f + 6.8f) / 6.8f;
static constexpr float MIATA_ANALOG_DIVIDER = (5.6f + 10.0f) / 10.0f;
// CLT and IAT: 2.7k pull-up to 5 V, and the 5.6k + 10k ADC divider loads the same node. The Thevenin equivalent of
// the two is a 4.26 V supply behind 2.30k, which is exactly the pull-up model rusEFI's thermistor code uses.
static constexpr float MIATA_TEMP_PULLUP = 2700.0f;
static constexpr float MIATA_TEMP_LOAD = 5600.0f + 10000.0f;
static constexpr float MIATA_TEMP_BIAS = MIATA_TEMP_PULLUP * MIATA_TEMP_LOAD / (MIATA_TEMP_PULLUP + MIATA_TEMP_LOAD);
static constexpr float MIATA_TEMP_SUPPLY = 5.0f * MIATA_TEMP_LOAD / (MIATA_TEMP_PULLUP + MIATA_TEMP_LOAD);
